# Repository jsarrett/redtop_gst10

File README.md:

## Signet Red Top speed sensor interface board for Garmin GST10/Nexus

This project is a small interface board so you can use a Garmin GST10 NMEA2000 interface with a signet RedTop speed sensor on a boat.  Eveything is through hole so hand soldering is easy.  My boat came with a signet sensor, but the display electronics died long ago.  This way I could install a modern N2K display, but not have to drill a new hole to change out the speed sensor Thru-hull fitting.  I assume if you have Nexus or NX2 displays, it will also work with them, but I haven't tested that.

# Project Status

- paddle wheel section works (tested on a sailboat up to 6ts, but tested on the bench up to ~30)
- temperature sensor is probably wrong.  I broke the Garmin one before I could characterize it so I just picked one that was close to my 1 datapoint (~25deg.C).  If you have a GST43 and some time to measure it, that would be greatly appreciated.

# How do I make one?
You can open the project with [KiCad](http://www.kicad-pcb.org), export a set of gerbers, and have PCBs manufactured.  [JLC PCB](http://www.jlcpcb.com) will make you some in a week or two for really cheap.  Then you can export a BOM, complete with DigiKey part numbers and put together an order for all the components.  When they arrive, you can solder them in the right places, and solder them in to your boat.  If you need help, just email me.  I may even have some spare PCBs lying around from my order.

This work is licensed under a [Creative Commons Attribution-ShareAlike 4.0 International License](http://creativecommons.org/licenses/by-sa/4.0/)

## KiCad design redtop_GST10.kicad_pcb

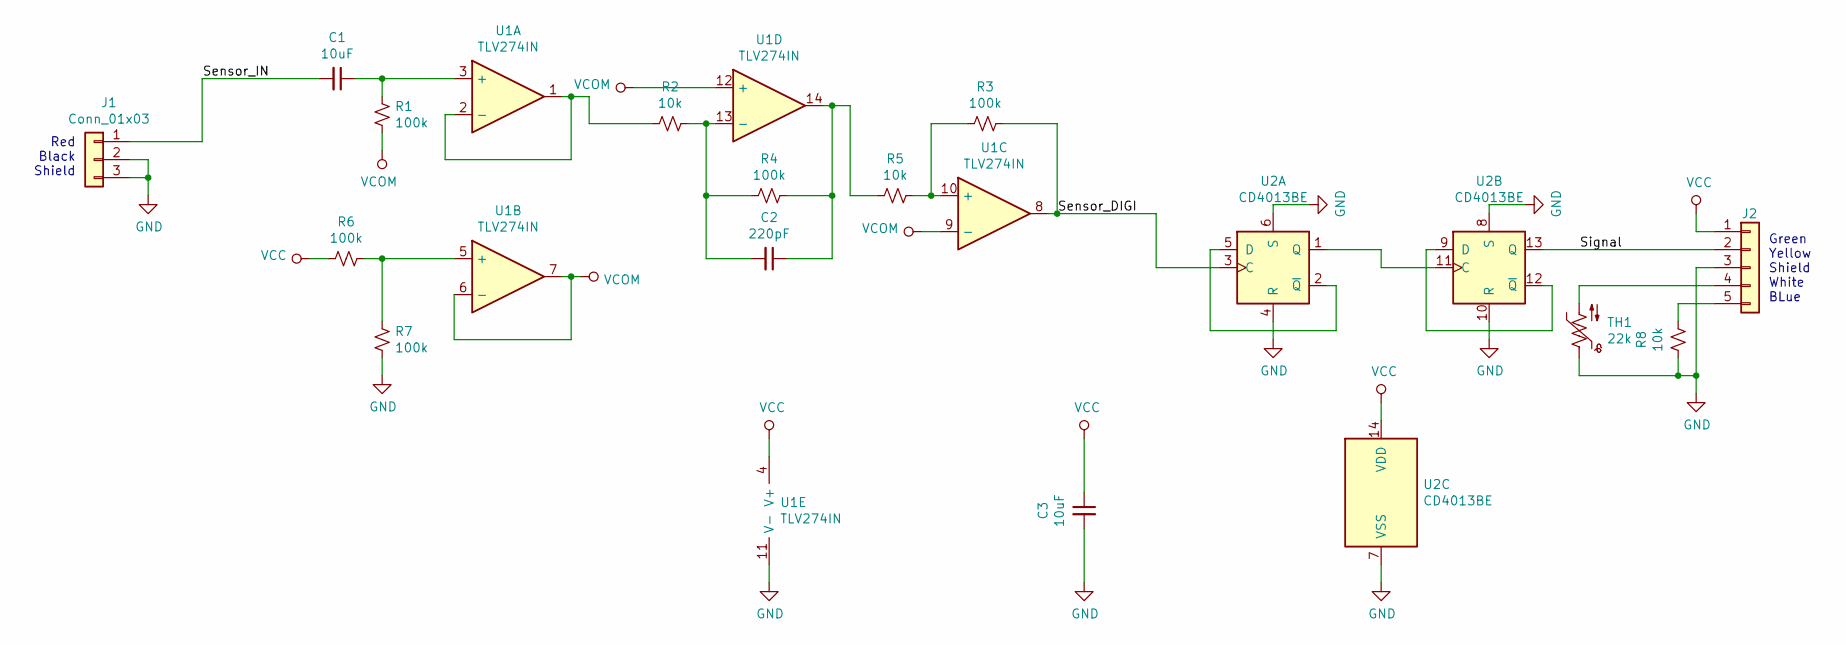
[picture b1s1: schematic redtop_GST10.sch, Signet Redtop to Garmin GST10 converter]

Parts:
C1, C3: 10uF; C_Disc_D4.3mm_W1.9mm_P5.00mm
C2: 220pF; C_Disc_D4.3mm_W1.9mm_P5.00mm
J1: Conn_01x03; PinHeader_1x03_P2.54mm_Vertical
J2: Conn_01x05; PinHeader_1x05_P2.54mm_Vertical
R1, R3, R4, R6, R7: 100k; R_Axial_DIN0207_L6.3mm_D2.5mm_P7.62mm_Horizontal
R2, R5, R8: 10k; R_Axial_DIN0207_L6.3mm_D2.5mm_P7.62mm_Horizontal
TH1: 22k; R_Axial_DIN0204_L3.6mm_D1.6mm_P2.54mm_Vertical
U1: TLV274IN; DIP-14_W7.62mm_LongPads
U2: CD4013BE; DIP-14_W7.62mm_LongPads

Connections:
/Sensor_DIGI: R3.2, U1.8, U2.3 (C)
/Sensor_IN: C1.2, J1.1
/Signal: J2.2, U2.13 (Q)
GND: C3.2, J1.2, J1.3, J2.3, R7.2, R8.1, TH1.1, U1.11 (V-), U2.4 (R), U2.6 (S), U2.7 (VSS), U2.8 (S), U2.10 (R)
unnamed: C1.1, R1.1, U1.3 (+)
unnamed: C2.1, R4.2, R5.1, U1.14
unnamed: C2.2, R2.2, R4.1, U1.13 (-)
unnamed: J2.4, TH1.2
unnamed: J2.5, R8.2
unnamed: R2.1, U1.1, U1.2 (-)
unnamed: R3.1, R5.2, U1.10 (+)
unnamed: R6.1, R7.1, U1.5 (+)
unnamed: U2.1 (Q), U2.11 (C)
unnamed: U2.2 (~Q), U2.5 (D)
unnamed: U2.9 (D), U2.12 (~Q)
VCC: C3.1, J2.1, R6.2, U1.4 (V+), U2.14 (VDD)
VCOM: R1.2, U1.6 (-), U1.7, U1.9 (-), U1.12 (+)

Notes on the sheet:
Green Yellow Shield White BLue
Red Black Shield

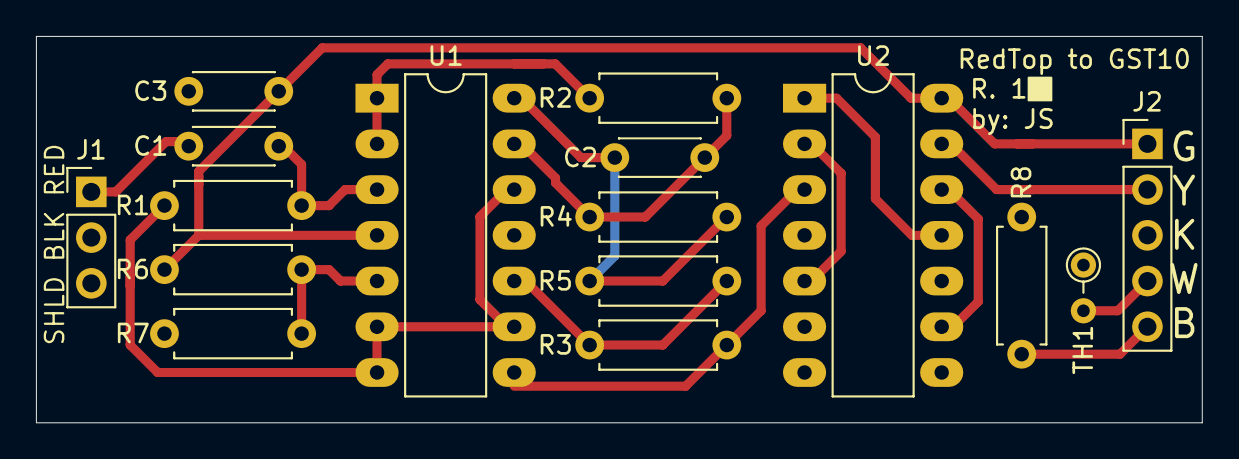
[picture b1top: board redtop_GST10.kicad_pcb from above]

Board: 2 copper layers, 64.8 x 21.5 mm, 16 parts (0 on the bottom side), 17 nets.

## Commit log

2020-01-25 boilerplate kicad gitignore
2020-01-25 inital pass at schematic. need to verify components, but ok to layout.
2020-01-30 update schematic with correct components and Part numbers
2020-01-30 initial layout attempt
2020-01-30 finalize r1 silkscreen
2020-02-16 update hysteresis resistor to as-built

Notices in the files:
README.md:
CC BY-SA 4.0
